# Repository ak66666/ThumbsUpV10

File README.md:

# ThumbsUp! v10 RP2040 Kailh Choc

Multilevel 44/46 Key Contoured Keyboard.
2- or 3-key Thumb Cluster.

* RP2040 is soldered on the board itself.
* Supports ProGlide Cirque touchpad.
* Hot swap sockets for switches.
* USB-C connector.
* Compact key spacing (18x17), large MX-size caps won't fit.
* Some keys on the lower PCB are tucked under the middle board to bring the index and middle fingers closer. That limits the choice of the key caps even more, only low profile would fit.

Other pictures in Photos folder.

# Firmware

Please refer to this article:
https://thumbsupkeyboards.blogspot.com/2024/02/source-files-and-default-firmware.html

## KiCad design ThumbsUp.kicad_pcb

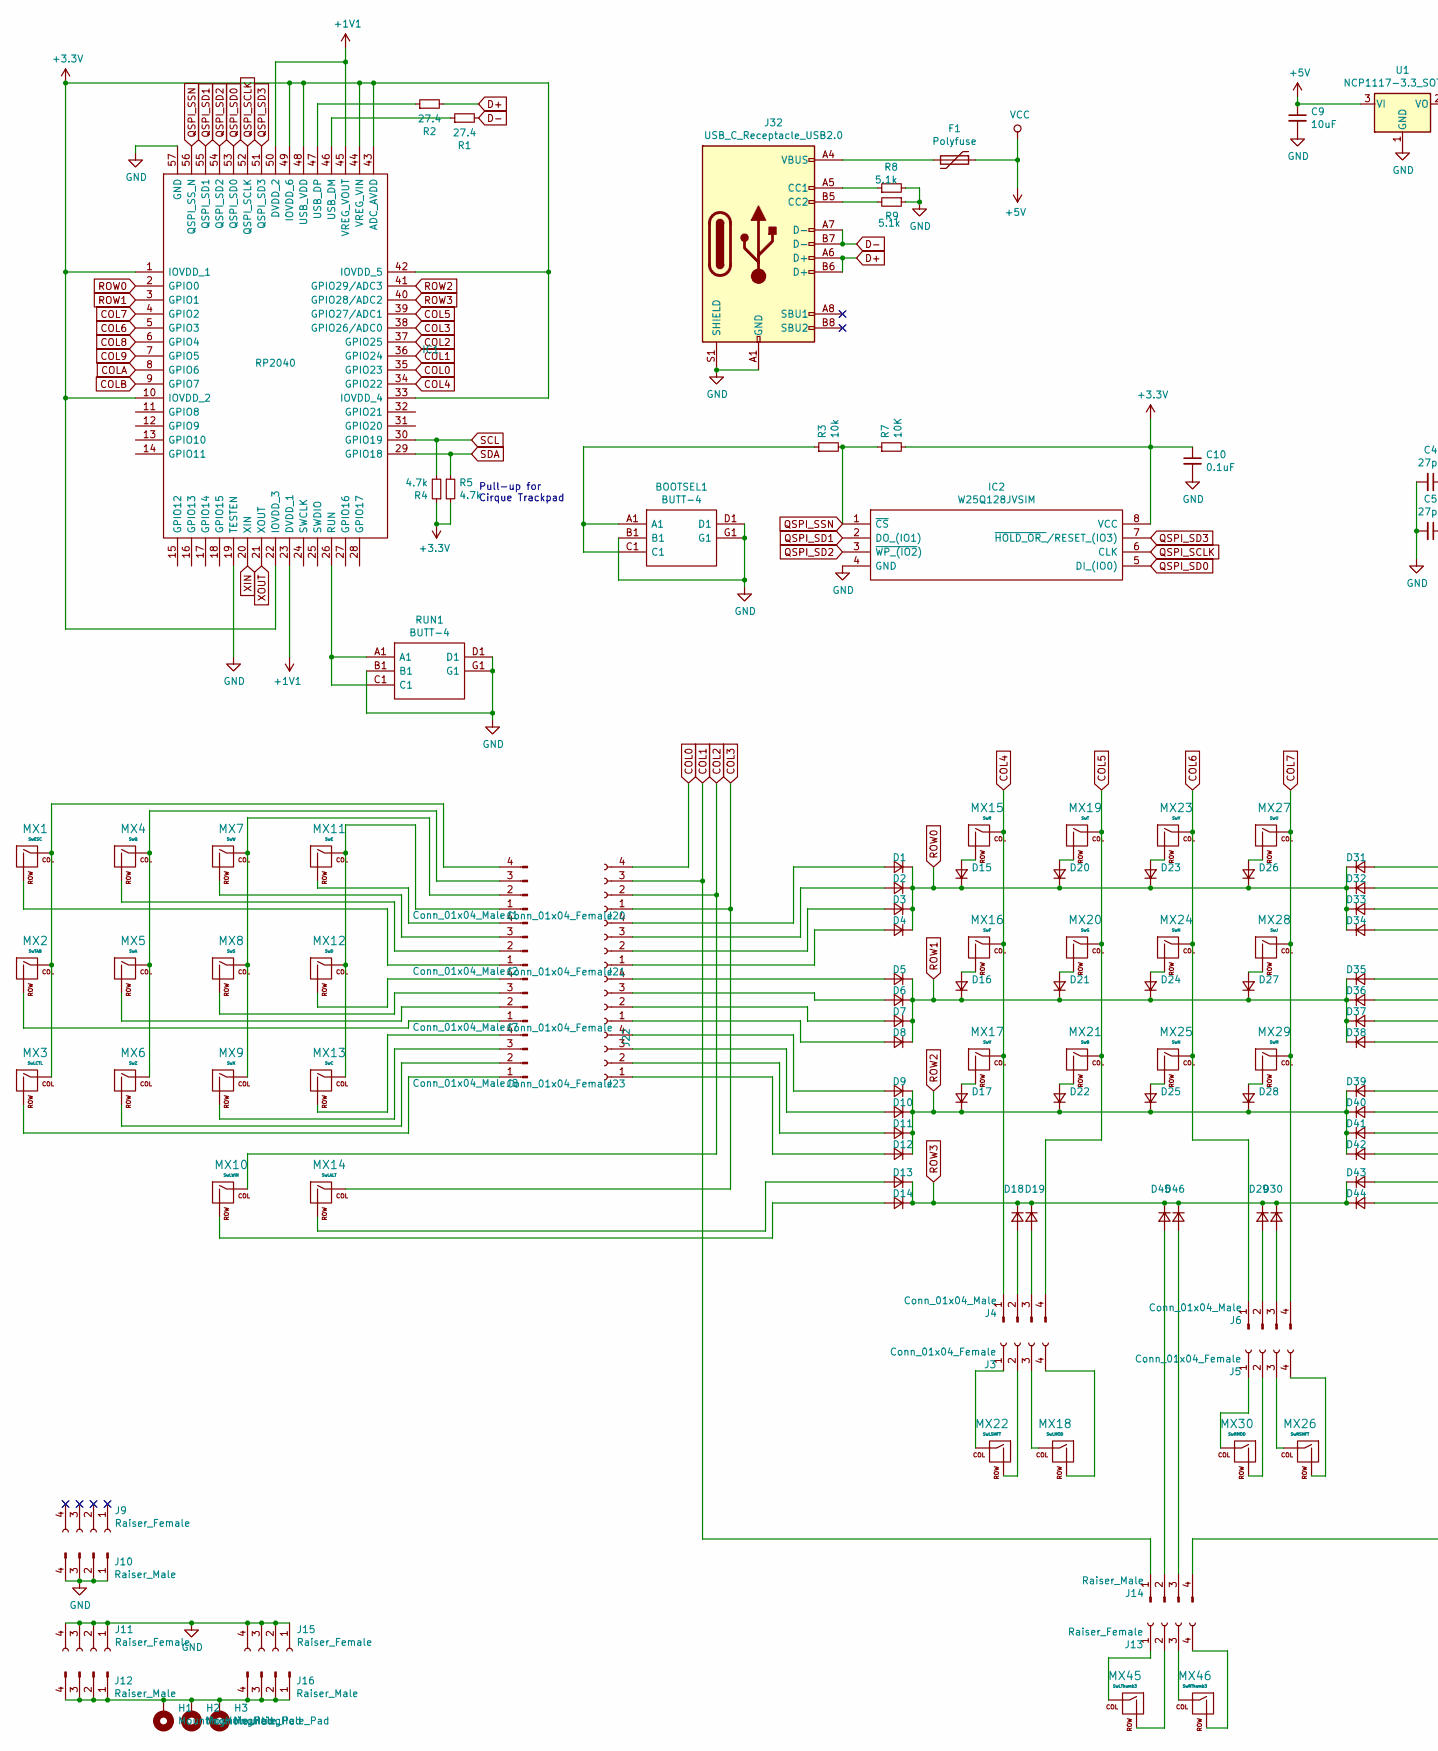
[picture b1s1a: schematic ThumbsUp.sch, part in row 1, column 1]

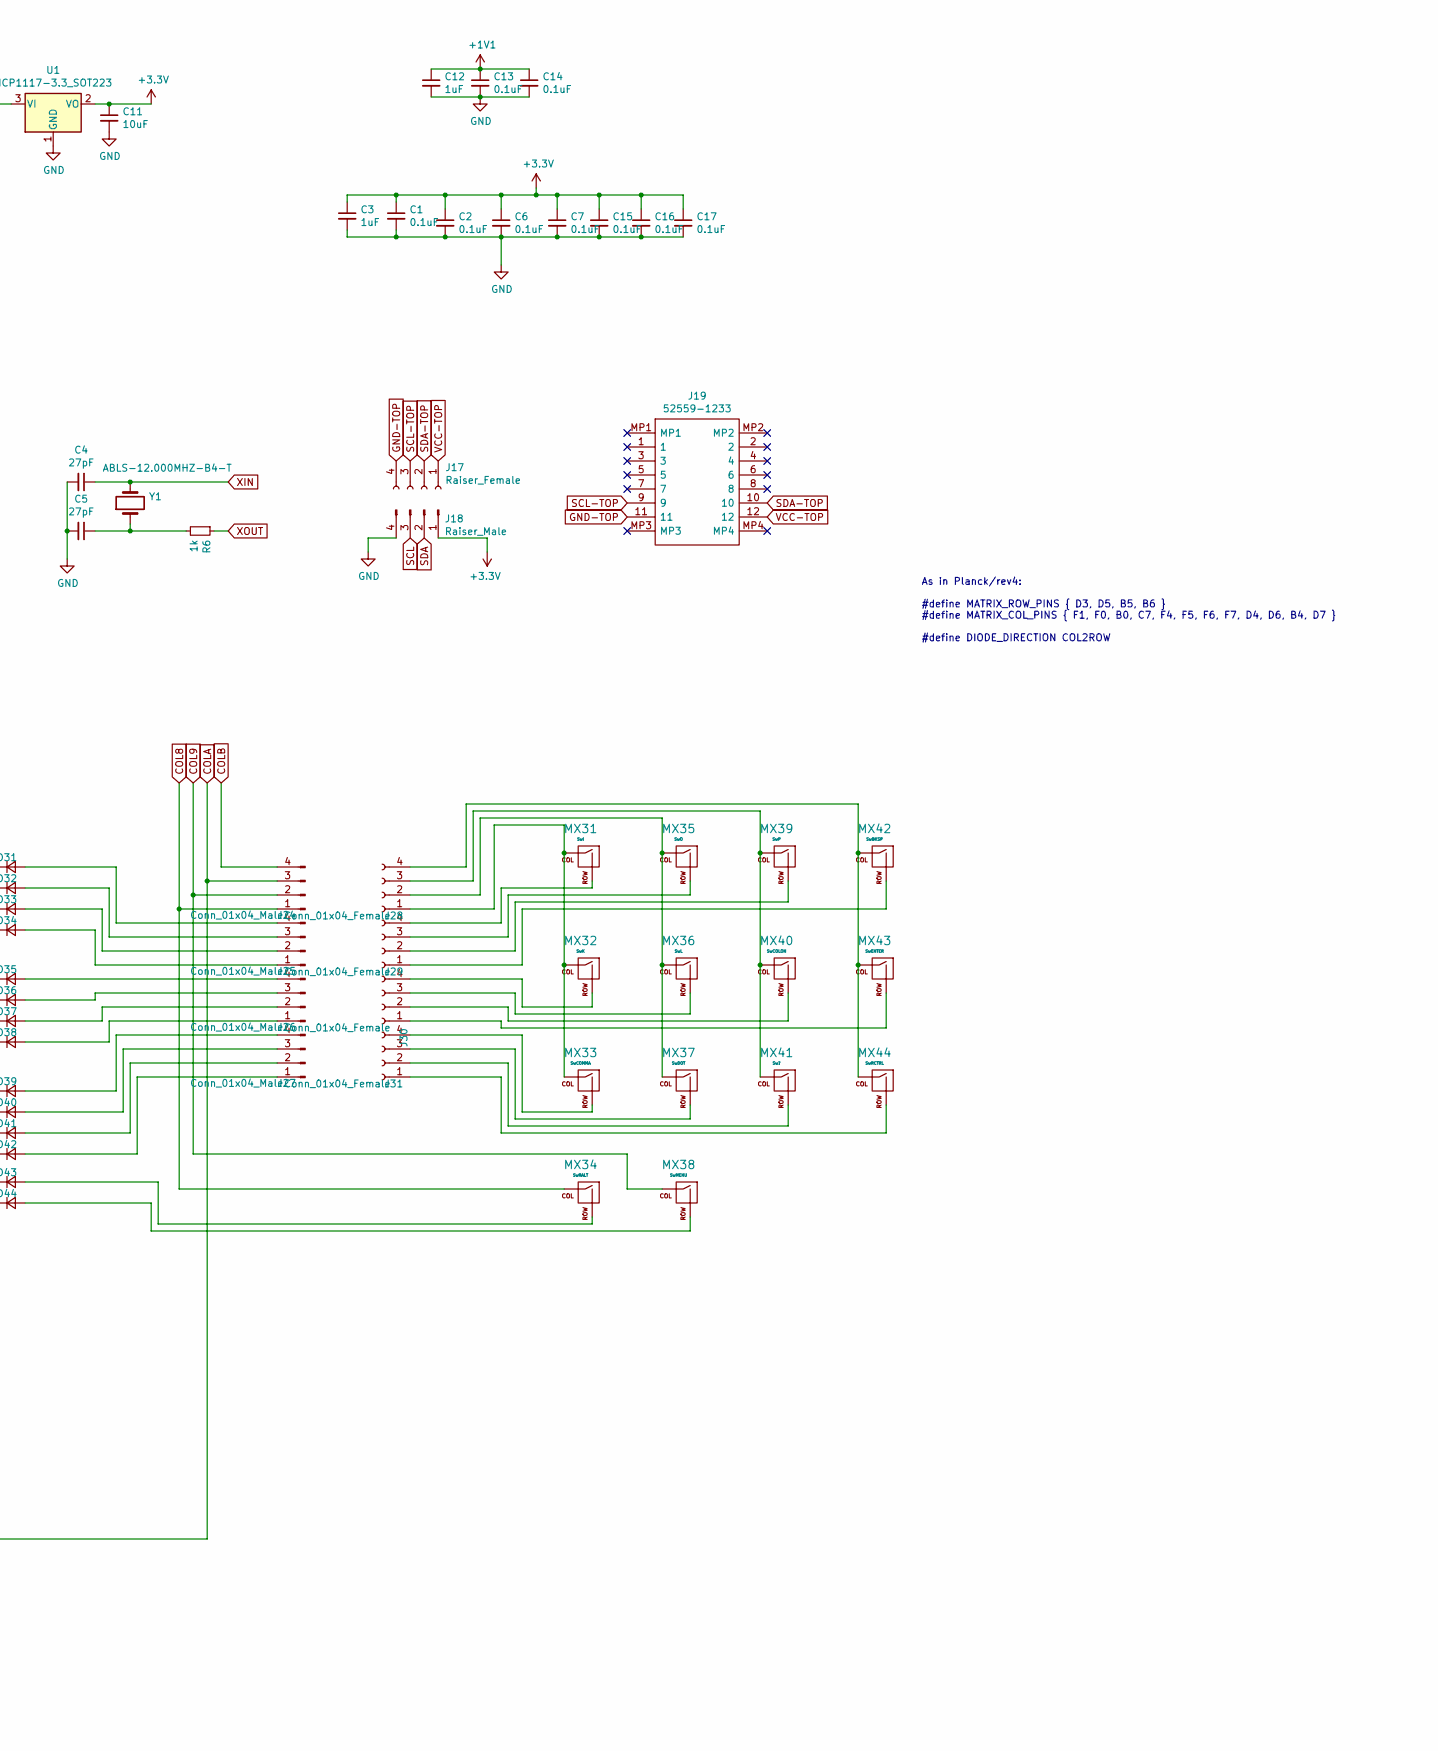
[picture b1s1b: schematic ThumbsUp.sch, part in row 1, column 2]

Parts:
BOOTSEL1: BUTT-4; BUTT4; Manufacturer_Part_Number BUTT-4; Mouser Part Number 992-BUTT-4
C1, C2, C6, C7, C10, C13, C14, C15, C16, C17: 0.1uF; C_0805_2012Metric
C3, C12: 1uF; C_0805_2012Metric
C4, C5: 27pF; C_0805_2012Metric
C9, C11: 10uF; C_0805_2012Metric
D1, D2, D3, D4, D5, D6, D7, D8, D9, D10, D11, D12, D13, D14, D15, D16, D17, D18, D19, D20, D21, D22, D23, D24, D25, D26, D27, D28, D29, D30, D31, D32, D33, D34, D35, D36, D37, D38, D39, D40, D41, D42, D43, D44, D45, D46: D_Small; D_SOD-123
F1: Polyfuse; Fuse_1206_3216Metric
H1, H2, H3: MountingHole_Pad; MountingHole_6.4mm_M6_Pad_Via
IC1: RP2040; QFN40P700X700X90-57N-D; Manufacturer_Part_Number RP2040
IC2: W25Q128JVSIM; SOIC127P790X216-8N; Manufacturer_Part_Number W25Q128JVSIM; Mouser Part Number 454-W25Q128JVSIM
J1, J2, J4, J6, J7, J8, J24, J25, J26, J27: Conn_01x04_Male; PinHeader_1x04_P2.54mm_Vertical
J3, J5, J20, J21, J22, J23, J28, J29, J30, J31: Conn_01x04_Female; PinSocket_1x04_P2.54mm_Vertical
J9, J11, J13, J15, J17: Raiser_Female; PinSocket_1x04_P2.54mm_Vertical
J10, J12, J14, J16, J18: Raiser_Male; PinHeader_1x04_P2.54mm_Vertical
J19: 52559-1233; 525591233; Mouser Part Number 538-52559-1233
J32: USB_C_Receptacle_USB2.0; USB_C_Receptacle_Palconn_UTC16-G
MX1: SwESC; Kailh_socket_PG1350
MX2: SwTAB; Kailh_socket_PG1350
MX3: SwLCTL; Kailh_socket_PG1350
MX4: SwQ; Kailh_socket_PG1350
MX5: SwA; Kailh_socket_PG1350
MX6: SwZ; Kailh_socket_PG1350
MX7: SwW; Kailh_socket_PG1350
MX8: SwS; Kailh_socket_PG1350
MX9: SwX; Kailh_socket_PG1350
MX10: SwLWIN; Kailh_socket_PG1350
MX11: SwE; Kailh_socket_PG1350
MX12: SwD; Kailh_socket_PG1350
MX13: SwC; Kailh_socket_PG1350
MX14: SwLALT; Kailh_socket_PG1350
MX15: SwR; Kailh_socket_PG1350
MX16: SwF; Kailh_socket_PG1350
MX17: SwV; Kailh_socket_PG1350
MX18: SwLMOD; Kailh_socket_PG1350
MX19: SwT; Kailh_socket_PG1350
MX20: SwG; Kailh_socket_PG1350
MX21: SwB; Kailh_socket_PG1350
MX22: SwLSHFT; Kailh_socket_PG1350
MX23: SwY; Kailh_socket_PG1350
MX24: SwH; Kailh_socket_PG1350
MX25: SwN; Kailh_socket_PG1350
MX26: SwRSHFT; Kailh_socket_PG1350
MX27: SwU; Kailh_socket_PG1350
MX28: SwJ; Kailh_socket_PG1350
MX29: SwM; Kailh_socket_PG1350
MX30: SwRMOD; Kailh_socket_PG1350
MX31: SwI; Kailh_socket_PG1350
MX32: SwK; Kailh_socket_PG1350
MX33: SwCOMMA; Kailh_socket_PG1350
MX34: SwRALT; Kailh_socket_PG1350
MX35: SwO; Kailh_socket_PG1350
MX36: SwL; Kailh_socket_PG1350
MX37: SwDOT; Kailh_socket_PG1350
MX38: SwMENU; Kailh_socket_PG1350
MX39: SwP; Kailh_socket_PG1350
MX40: SwCOLON; Kailh_socket_PG1350
MX41: Sw?; Kailh_socket_PG1350
MX42: SwBKSP; Kailh_socket_PG1350
MX43: SwENTER; Kailh_socket_PG1350
MX44: SwRCTRL; Kailh_socket_PG1350
MX45: SwLThumb3; Kailh_socket_PG1350
MX46: SwRThumb3; Kailh_socket_PG1350
R1, R2: 27.4; R_0805_2012Metric
R3: 10k; R_0805_2012Metric
R4, R5: 4.7k; R_0805_2012Metric
R6: 1k; R_0805_2012Metric
R7: 10K; R_0805_2012Metric
R8, R9: 5.1k; R_0805_2012Metric
RUN1: BUTT-4; BUTT4; Manufacturer_Part_Number BUTT-4; Mouser Part Number 992-BUTT-4
U1: NCP1117-3.3_SOT223; SOT-223-3_TabPin2
Y1: ABLS-12.000MHZ-B4-T; HC%2f49US-(AT49)_1

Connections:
+1V1: C12.1, C13.1, C14.1, IC1.23 (DVDD_1), IC1.45 (VREG_VOUT), IC1.50 (DVDD_2)
+3V3: C1.1, C2.1, C3.1, C6.1, C7.1, C10.1, C11.1, C15.1, C16.1, C17.1, IC1.1 (IOVDD_1), IC1.10 (IOVDD_2), IC1.22 (IOVDD_3), IC1.33 (IOVDD_4), IC1.42 (IOVDD_5), IC1.43 (ADC_AVDD), IC1.44 (VREG_VIN), IC1.48 (USB_VDD), IC1.49 (IOVDD_6), IC2.8 (VCC), J18.1, R4.1, R5.2, R7.2, U1.2 (VO)
+5V: C9.1, F1.1, U1.3 (VI)
COL0: IC1.35 (GPIO23), J20.4
COL1: IC1.36 (GPIO24), J14.1, J20.3
COL2: IC1.37 (GPIO25), J20.2, MX10.1 (COL)
COL3: IC1.38 (GPIO26/ADC0), J20.1, MX14.1 (COL)
COL4: IC1.34 (GPIO22), J4.1, MX15.1 (COL), MX16.1 (COL), MX17.1 (COL)
COL5: IC1.39 (GPIO27/ADC1), J4.4, MX19.1 (COL), MX20.1 (COL), MX21.1 (COL)
COL6: IC1.5 (GPIO3), J6.1, MX23.1 (COL), MX24.1 (COL), MX25.1 (COL)
COL7: IC1.4 (GPIO2), J6.4, MX27.1 (COL), MX28.1 (COL), MX29.1 (COL)
COL8: IC1.6 (GPIO4), J24.1, MX34.1 (COL)
COL9: IC1.7 (GPIO5), J24.2, MX38.1 (COL)
COLA: IC1.8 (GPIO6), J14.4, J24.3
COLB: IC1.9 (GPIO7), J24.4
D+: J32.A6 (D+), J32.B6 (D+), R2.2
D-: J32.A7 (D-), J32.B7 (D-), R1.2
GND: BOOTSEL1.B1, BOOTSEL1.D1, BOOTSEL1.G1, C1.2, C2.2, C3.2, C4.2, C5.2, C6.2, C7.2, C9.2, C10.2, C11.2, C12.2, C13.2, C14.2, C15.2, C16.2, C17.2, IC1.19 (TESTEN), IC1.57 (GND), IC2.4 (GND), J10.1, J10.2, J10.3, J10.4, J11.1, J11.2, J11.3, J11.4, J15.1, J15.2, J15.3, J15.4, J18.4, J32.A1 (GND), J32.A12 (GND), J32.B1 (GND), J32.B12 (GND), J32.S1 (SHIELD), R8.2, R9.1, RUN1.B1, RUN1.D1, RUN1.G1, U1.1 (GND)
GND-TOP: J17.4, J19.11; also elsewhere on the board
unnamed: BOOTSEL1.A1, BOOTSEL1.C1, R3.1
unnamed: C5.1, R6.2, Y1.1
unnamed: D1.2 (A), J21.4
unnamed: D2.2 (A), J21.3
unnamed: D3.2 (A), J21.2
unnamed: D4.2 (A), J21.1
unnamed: D5.2 (A), J22.4
unnamed: D6.2 (A), J22.3
unnamed: D7.2 (A), J22.2
unnamed: D8.2 (A), J22.1
unnamed: D9.2 (A), J23.4
unnamed: D10.2 (A), J23.3
unnamed: D11.2 (A), J23.2
unnamed: D12.2 (A), J23.1
unnamed: D13.2 (A), MX14.2 (ROW)
unnamed: D14.2 (A), MX10.2 (ROW)
unnamed: D15.2 (A), MX15.2 (ROW)
unnamed: D16.2 (A), MX16.2 (ROW)
unnamed: D17.2 (A), MX17.2 (ROW)
unnamed: D18.2 (A), J4.2
unnamed: D19.2 (A), J4.3
unnamed: D20.2 (A), MX19.2 (ROW)
unnamed: D21.2 (A), MX20.2 (ROW)
unnamed: D22.2 (A), MX21.2 (ROW)
unnamed: D23.2 (A), MX23.2 (ROW)
unnamed: D24.2 (A), MX24.2 (ROW)
unnamed: D25.2 (A), MX25.2 (ROW)
unnamed: D26.2 (A), MX27.2 (ROW)
unnamed: D27.2 (A), MX28.2 (ROW)
unnamed: D28.2 (A), MX29.2 (ROW)
unnamed: D29.2 (A), J6.2
unnamed: D30.2 (A), J6.3
unnamed: D31.2 (A), J25.4
unnamed: D32.2 (A), J25.3
unnamed: D33.2 (A), J25.2
unnamed: D34.2 (A), J25.1
unnamed: D35.2 (A), J26.4
unnamed: D36.2 (A), J26.3
unnamed: D37.2 (A), J26.2
unnamed: D38.2 (A), J26.1
unnamed: D39.2 (A), J27.4
unnamed: D40.2 (A), J27.3
unnamed: D41.2 (A), J27.2
unnamed: D42.2 (A), J27.1
unnamed: D43.2 (A), MX34.2 (ROW)
unnamed: D44.2 (A), MX38.2 (ROW)
unnamed: D45.2 (A), J14.2
unnamed: D46.2 (A), J14.3
unnamed: F1.2, J32.A4 (VBUS), J32.A9 (VBUS), J32.B4 (VBUS), J32.B9 (VBUS)
unnamed: H1.1, H2.1, H3.1, J12.1, J12.2, J12.3, J12.4, J16.1, J16.2, J16.3, J16.4
unnamed: IC1.26 (RUN), RUN1.A1, RUN1.C1
unnamed: IC1.46 (USB_DM), R1.1
unnamed: IC1.47 (USB_DP), R2.1
unnamed: J1.1, MX11.1 (COL), MX12.1 (COL), MX13.1 (COL)
unnamed: J1.2, MX7.1 (COL), MX8.1 (COL), MX9.1 (COL)
unnamed: J1.3, MX4.1 (COL), MX5.1 (COL), MX6.1 (COL)
unnamed: J1.4, MX1.1 (COL), MX2.1 (COL), MX3.1 (COL)
unnamed: J2.1, MX1.2 (ROW)
unnamed: J2.2, MX4.2 (ROW)
unnamed: J2.3, MX7.2 (ROW)
unnamed: J2.4, MX11.2 (ROW)
unnamed 80: J3.1, MX22.1 (COL); also elsewhere on the board
unnamed 81: J3.2, MX22.2 (ROW); also elsewhere on the board
unnamed 82: J3.3, MX18.1 (COL); also elsewhere on the board
unnamed 83: J3.4, MX18.2 (ROW); also elsewhere on the board
unnamed 84: J5.1, MX30.1 (COL); also elsewhere on the board
unnamed 85: J5.2, MX30.2 (ROW); also elsewhere on the board
unnamed 86: J5.3, MX26.1 (COL); also elsewhere on the board
unnamed 87: J5.4, MX26.2 (ROW); also elsewhere on the board
unnamed: J7.1, MX2.2 (ROW)
unnamed: J7.2, MX5.2 (ROW)
unnamed: J7.3, MX8.2 (ROW)
unnamed: J7.4, MX12.2 (ROW)
unnamed: J8.1, MX3.2 (ROW)
unnamed: J8.2, MX6.2 (ROW)
unnamed: J8.3, MX9.2 (ROW)
unnamed: J8.4, MX13.2 (ROW)
unnamed 96: J9.1; also elsewhere on the board
unnamed 97: J9.2; also elsewhere on the board
unnamed 98: J9.3; also elsewhere on the board
unnamed 99: J9.4; also elsewhere on the board
unnamed 100: J13.1, MX45.1 (COL); also elsewhere on the board
unnamed 101: J13.2, MX45.2 (ROW); also elsewhere on the board
unnamed 102: J13.3, MX46.1 (COL); also elsewhere on the board
unnamed 103: J13.4, MX46.2 (ROW); also elsewhere on the board
unnamed 104: J19.1; also elsewhere on the board
unnamed 105: J19.2; also elsewhere on the board
unnamed 106: J19.3; also elsewhere on the board
unnamed 107: J19.4; also elsewhere on the board
unnamed 108: J19.5; also elsewhere on the board
unnamed 109: J19.6; also elsewhere on the board
unnamed 110: J19.7; also elsewhere on the board
unnamed 111: J19.8; also elsewhere on the board
unnamed 112: J19.MP1; also elsewhere on the board
unnamed 113: J19.MP2; also elsewhere on the board
unnamed 114: J19.MP3; also elsewhere on the board
unnamed 115: J19.MP4; also elsewhere on the board
unnamed: J28.1, MX31.1 (COL), MX32.1 (COL), MX33.1 (COL)
unnamed: J28.2, MX35.1 (COL), MX36.1 (COL), MX37.1 (COL)
unnamed: J28.3, MX39.1 (COL), MX40.1 (COL), MX41.1 (COL)
unnamed: J28.4, MX42.1 (COL), MX43.1 (COL), MX44.1 (COL)
unnamed: J29.1, MX42.2 (ROW)
unnamed: J29.2, MX39.2 (ROW)
unnamed: J29.3, MX35.2 (ROW)
unnamed: J29.4, MX31.2 (ROW)
unnamed: J30.1, MX43.2 (ROW)
unnamed: J30.2, MX40.2 (ROW)
unnamed: J30.3, MX36.2 (ROW)
unnamed: J30.4, MX32.2 (ROW)
unnamed: J31.1, MX44.2 (ROW)
unnamed: J31.2, MX41.2 (ROW)
unnamed: J31.3, MX37.2 (ROW)
unnamed: J31.4, MX33.2 (ROW)
unnamed: J32.A5 (CC1), R8.1
unnamed: J32.B5 (CC2), R9.2
QSPI_SCLK: IC1.52 (QSPI_SCLK), IC2.6 (CLK)
QSPI_SD0: IC1.53 (QSPI_SD0), IC2.5 (DI_(IO0))
QSPI_SD1: IC1.55 (QSPI_SD1), IC2.2 (DO_(IO1))
QSPI_SD2: IC1.54 (QSPI_SD2), IC2.3 (~WP_(IO2))
QSPI_SD3: IC1.51 (QSPI_SD3), IC2.7 (~HOLD_OR_~/RESET_(IO3))
QSPI_SSN: IC1.56 (QSPI_SS_N), IC2.1 (~CS), R3.2, R7.1
ROW0: D1.1 (K), D2.1 (K), D3.1 (K), D4.1 (K), D15.1 (K), D20.1 (K), D23.1 (K), D26.1 (K), D31.1 (K), D32.1 (K), D33.1 (K), D34.1 (K), IC1.2 (GPIO0)
ROW1: D5.1 (K), D6.1 (K), D7.1 (K), D8.1 (K), D16.1 (K), D21.1 (K), D24.1 (K), D27.1 (K), D35.1 (K), D36.1 (K), D37.1 (K), D38.1 (K), IC1.3 (GPIO1)
ROW2: D9.1 (K), D10.1 (K), D11.1 (K), D12.1 (K), D17.1 (K), D22.1 (K), D25.1 (K), D28.1 (K), D39.1 (K), D40.1 (K), D41.1 (K), D42.1 (K), IC1.41 (GPIO29/ADC3)
ROW3: D13.1 (K), D14.1 (K), D18.1 (K), D19.1 (K), D29.1 (K), D30.1 (K), D43.1 (K), D44.1 (K), D45.1 (K), D46.1 (K), IC1.40 (GPIO28/ADC2)
SCL: IC1.30 (GPIO19), J18.3, R4.2
SCL-TOP: J17.3, J19.9; also elsewhere on the board
SDA: IC1.29 (GPIO18), J18.2, R5.1
SDA-TOP: J17.2, J19.10; also elsewhere on the board
VCC-TOP: J17.1, J19.12; also elsewhere on the board
XIN: C4.1, IC1.20 (XIN), Y1.2
XOUT: IC1.21 (XOUT), R6.1

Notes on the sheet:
As in Planck/rev4: #define MATRIX_ROW_PINS { D3, D5, B5, B6 } #define MATRIX_COL_PINS { F1, F0, B0, C7, F4, F5, F6, F7, D4, D6, B4, D7 } #define DIODE_DIRECTION COL2ROW
Pull-up for Cirque Trackpad

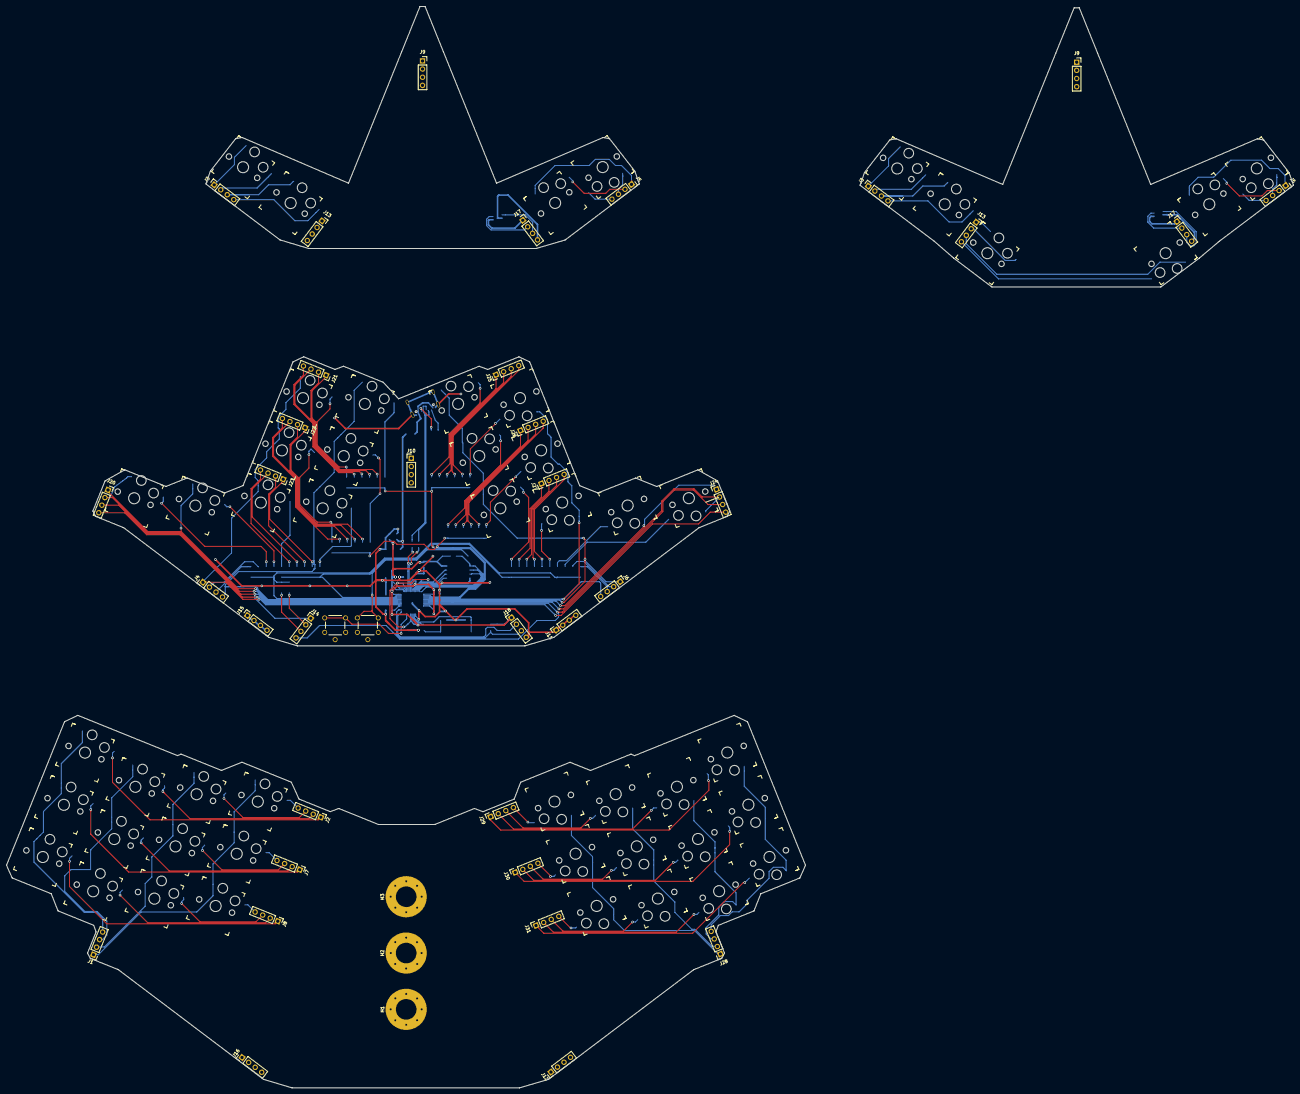
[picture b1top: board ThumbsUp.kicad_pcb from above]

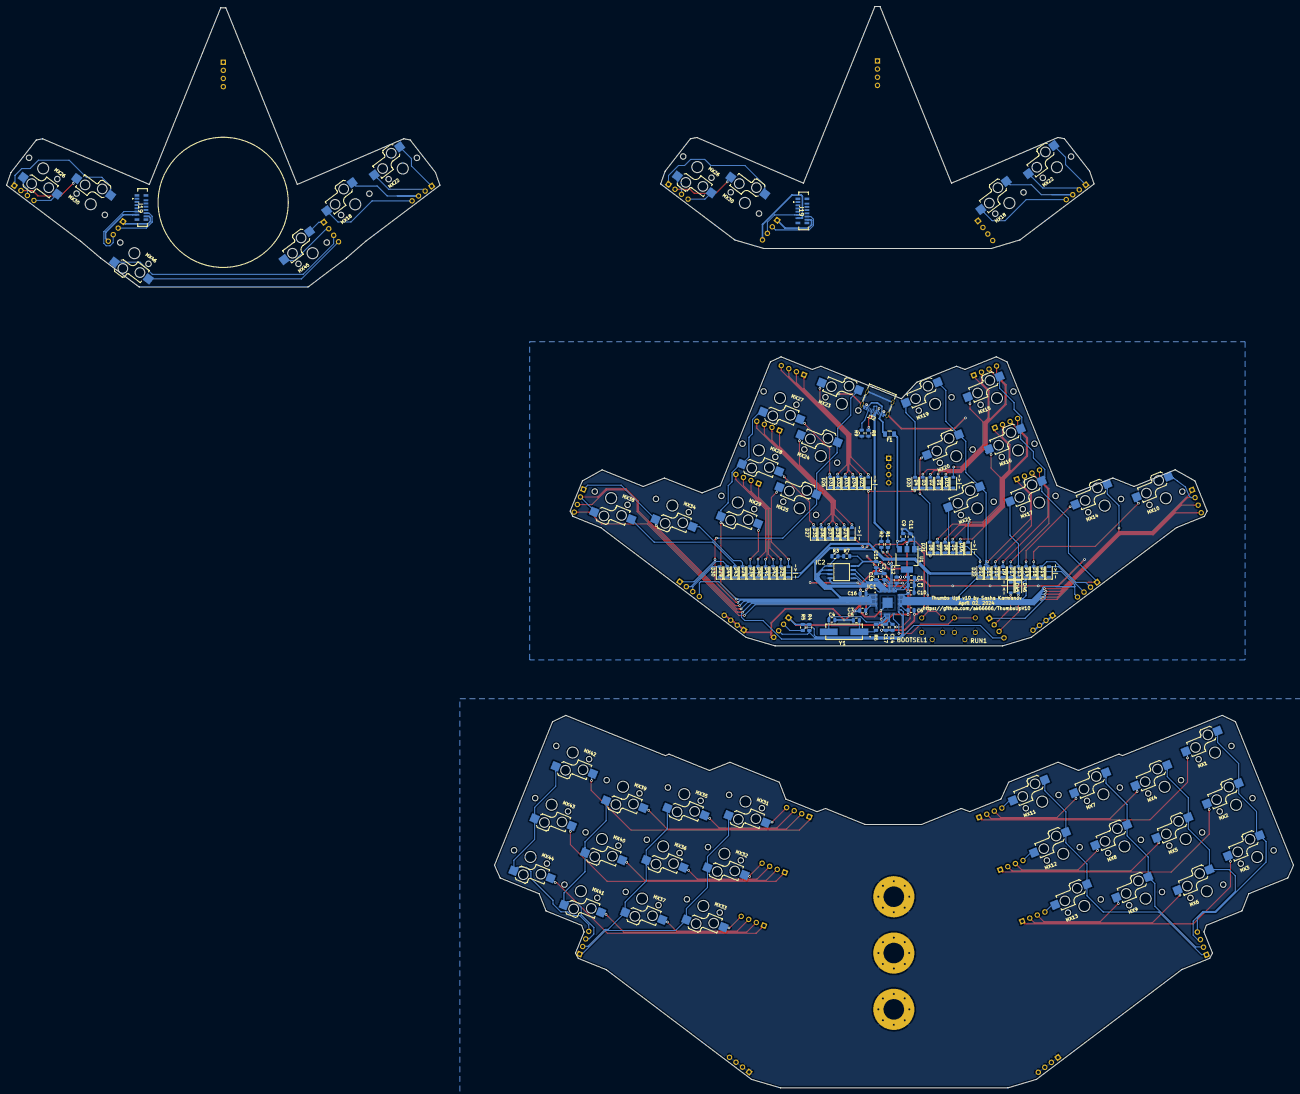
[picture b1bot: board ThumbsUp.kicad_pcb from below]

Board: 2 copper layers, 400.0 x 336.1 mm, 169 parts (79 on the bottom side), 151 nets.

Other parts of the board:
J3#2, J5#2: Conn_01x04_Female; PinSocket_1x04_P2.54mm_Vertical
J9#2, J13#2, J17#2: Raiser_Female; PinSocket_1x04_P2.54mm_Vertical
J19#2: 52559-1233; 525591233
MX18#2: SwLMOD; Kailh_socket_PG1350
MX22#2: SwLSHFT; Kailh_socket_PG1350
MX26#2: SwRSHFT; Kailh_socket_PG1350
MX30#2: SwRMOD; Kailh_socket_PG1350

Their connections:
GND-TOP: J17#2.4, J19#2.11; also elsewhere on the board
unnamed 80: J3#2.1, MX22#2.1; also elsewhere on the board
unnamed 81: J3#2.2, MX22#2.2; also elsewhere on the board
unnamed 82: J3#2.3, MX18#2.1; also elsewhere on the board
unnamed 83: J3#2.4, MX18#2.2; also elsewhere on the board
unnamed 84: J5#2.1, MX30#2.1; also elsewhere on the board
unnamed 85: J5#2.2, MX30#2.2; also elsewhere on the board
unnamed 86: J5#2.3, MX26#2.1; also elsewhere on the board
unnamed 87: J5#2.4, MX26#2.2; also elsewhere on the board
unnamed 96: J9#2.1; also elsewhere on the board
unnamed 97: J9#2.2; also elsewhere on the board
unnamed 98: J9#2.3; also elsewhere on the board
unnamed 99: J9#2.4; also elsewhere on the board
unnamed 100: J13#2.1; also elsewhere on the board
unnamed 101: J13#2.2; also elsewhere on the board
unnamed 102: J13#2.3; also elsewhere on the board
unnamed 103: J13#2.4; also elsewhere on the board
unnamed 104: J19#2.1; also elsewhere on the board
unnamed 105: J19#2.2; also elsewhere on the board
unnamed 106: J19#2.3; also elsewhere on the board
unnamed 107: J19#2.4; also elsewhere on the board
unnamed 108: J19#2.5; also elsewhere on the board
unnamed 109: J19#2.6; also elsewhere on the board
unnamed 110: J19#2.7; also elsewhere on the board
unnamed 111: J19#2.8; also elsewhere on the board
unnamed 112: J19#2.MP1; also elsewhere on the board
unnamed 113: J19#2.MP2; also elsewhere on the board
unnamed 114: J19#2.MP3; also elsewhere on the board
unnamed 115: J19#2.MP4; also elsewhere on the board
SCL-TOP: J17#2.3, J19#2.9; also elsewhere on the board
SDA-TOP: J17#2.2, J19#2.10; also elsewhere on the board
VCC-TOP: J17#2.1, J19#2.12; also elsewhere on the board

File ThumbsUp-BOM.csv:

"Id";"Designator";"Package";"Quantity";"Designation";"Supplier and ref";
1;"R9,R8";"R_0805_2012Metric";2;"5.1k";;;
2;"J32";"USB_C_Receptacle_Palconn_UTC16-G";1;"USB_C_Receptacle_USB2.0";;;
3;"RUN1,BOOTSEL1";"TL1016AAF220QG";2;"TL1016AAF220QG";;;
4;"IC1";"QFN40P700X700X90-57N-D";1;"RP2040";;;
5;"D25,D44,D43,D42,D41,D40,D39,D38,D37,D36,D35,D34,D33,D32,D31,D30,D29,D28,D27,D26,D24,D23,D22,D21,D20,D19,D18,D17,D16,D15,D14,D13,D12,D11,D10,D9,D8,D7,D6,D5,D4,D3,D2,D1";"D_SOD-123";44;"D_Small";;;
6;"Y1";"HC%2f49US-(AT49)_1";1;"ABLS-12.000MHZ-B4-T";;;
7;"R3";"R_0805_2012Metric";1;"10k";;;
8;"IC2";"SOIC127P790X216-8N";1;"W25Q128JVSIM";;;
9;"C9,C11";"C_0805_2012Metric";2;"10uF";;;
10;"C7,C6,C2,C1,C17,C16,C15,C14,C13,C10";"C_0805_2012Metric";10;"0.1uF";;;
11;"C5,C4";"C_0805_2012Metric";2;"27pF";;;
12;"C3,C12";"C_0805_2012Metric";2;"1uF";;;
13;"U1";"SOT-223-3_TabPin2";1;"NCP1117-3.3_SOT223";;;
14;"R7";"R_0805_2012Metric";1;"DNF";;;
15;"R6";"R_0805_2012Metric";1;"1k";;;
16;"R5,R4";"R_0805_2012Metric";2;"4.7k";;;
17;"R2,R1";"R_0805_2012Metric";2;"27.4";;;
18;"F1";"Fuse_1206_3216Metric";1;"Polyfuse";;;
19;"J27,J24,J25,J26,J6,J4";"PinHeader_1x04_P2.54mm_Vertical";6;"Conn_01x04_Male";;;
20;"J18,J10,J14";"PinHeader_1x04_P2.54mm_Vertical";3;"Raiser_Male";;;
21;"MX38";"Kailh_socket_PG1350_optional";1;"SwMENU";;;
22;"MX27";"Kailh_socket_PG1350_optional";1;"SwU";;;
23;"MX28";"Kailh_socket_PG1350_optional";1;"SwJ";;;
24;"MX29";"Kailh_socket_PG1350_optional";1;"SwM";;;
25;"MX34";"Kailh_socket_PG1350_optional";1;"SwRALT";;;
26;"J20,J21,J22,J23";"PinSocket_1x04_P2.54mm_Vertical";4;"Conn_01x04_Female";;;
27;"MX15";"Kailh_socket_PG1350_optional";1;"SwR";;;
28;"MX24";"Kailh_socket_PG1350_optional";1;"SwH";;;
29;"MX10";"Kailh_socket_PG1350_optional";1;"SwLWIN";;;
30;"MX14";"Kailh_socket_PG1350_optional";1;"SwLALT";;;
31;"MX17";"Kailh_socket_PG1350_optional";1;"SwV";;;
32;"MX25";"Kailh_socket_PG1350_optional";1;"SwN";;;
33;"MX19";"Kailh_socket_PG1350_optional";1;"SwT";;;
34;"MX21";"Kailh_socket_PG1350_optional";1;"SwB";;;
35;"MX20";"Kailh_socket_PG1350_optional";1;"SwG";;;
36;"MX23";"Kailh_socket_PG1350_optional";1;"SwY";;;
37;"MX16";"Kailh_socket_PG1350_optional";1;"SwF";;;
38;"J15,J11";"PinSocket_1x04_P2.54mm_Vertical";2;"Raiser_Female";;;

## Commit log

2024-04-02 ThumbsUp! v10 started
2024-04-05 ThumbsUp! v10 moved the keys around
2024-04-09 Redefined boundaries of the middle PCB.
2024-04-12 Redefined boundaries of the lower PCB.
2024-04-20 Traced bottom PCB.
2024-04-21 Traced middle PCB.
2024-04-21 Traced top PCB, tweaked tracks here and there.
2024-04-25 Added silkscreens.
2024-04-25 Added Gerbers.
2024-04-25 Fixed BOM.
2025-02-27 ThumbsUp v10: Added photos, updated description.
